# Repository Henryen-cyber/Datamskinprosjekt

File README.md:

# Datamaskinprosjekt

Bitstreams for FPGA are located [here](./FPGA/bitstreams/).

Hex for MCU are packaged in the Github releases.

## [The Report](./Rapport_Gruppe2_TDT4295_Datamaskinprosjekt.pdf)

## PCB KiCAD Checkout

When working on a KiCAD File ALWAYS update this table to state that you are working on it

| KiCAD File | Checkout Status          | Checkout/-in Date | Checked out by |
| ---------- | ------------------------ | ----------------- | -------------- |
| Example1   | :red_circle: Checked Out | 12.11.2023        | John Doe       |
| Example2   | :green_circle: Available | 01.09.2023        | Jane Doe       |

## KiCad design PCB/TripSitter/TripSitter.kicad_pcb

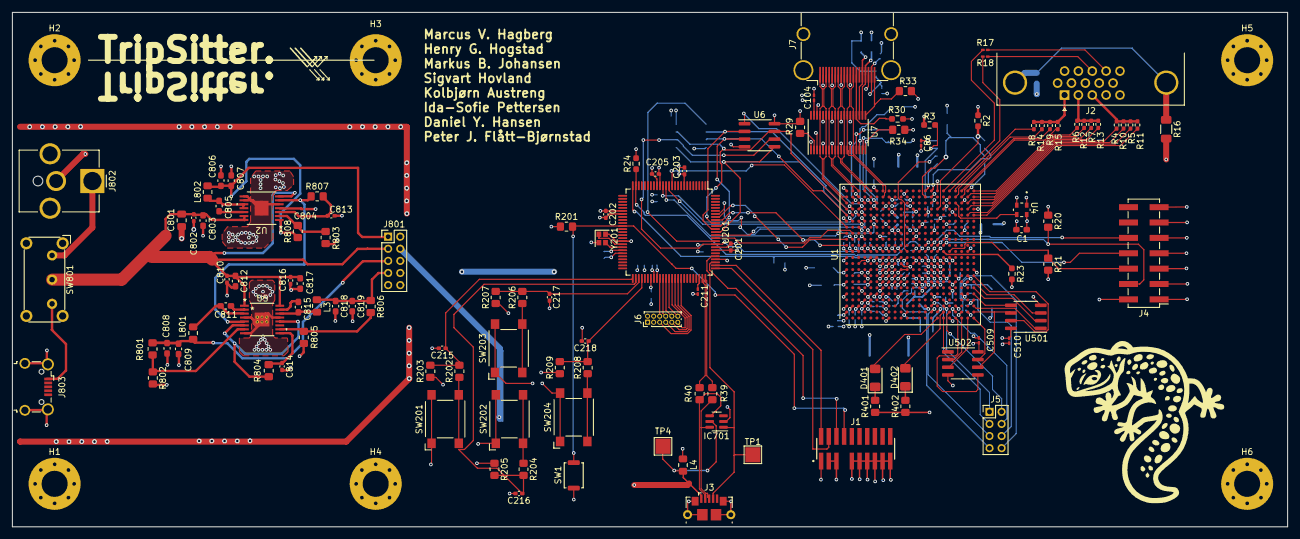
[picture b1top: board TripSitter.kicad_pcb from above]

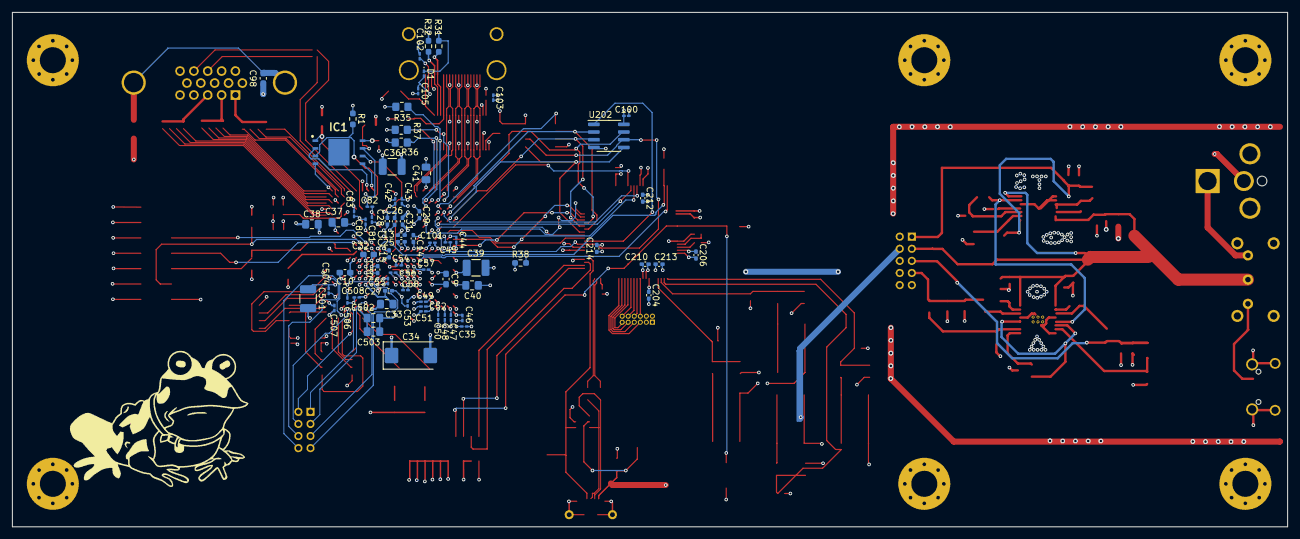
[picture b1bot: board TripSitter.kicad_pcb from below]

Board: 4 copper layers, 210.7 x 85.0 mm, 192 parts (72 on the bottom side), 147 nets.

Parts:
C1, C803, C805, C811, C812, C815, C817: 0.1uF; C_0603_1608Metric_Pad1.08x0.95mm_HandSolder
C9, C10, C32: 47uF; C_0603_1608Metric_Pad1.08x0.95mm_HandSolder
C13, C14, C15, C25, C26, C27, C30: 470nF; C_0402_1005Metric_Pad0.74x0.62mm_HandSolder
C28, C29, C31: 4.7uF; C_0402_1005Metric_Pad0.74x0.62mm_HandSolder
C33, C801: 100uF; C_0805_2012Metric_Pad1.18x1.45mm_HandSolder
C34: 330uF; CP_EIA-7343-43_Kemet-X_Pad2.25x2.55mm_HandSolder
C35, C46, C47, C48, C49, C50: 4.7uF; C_0201_0603Metric_Pad0.64x0.40mm_HandSolder
C36, C39, C501: 47uF; C_1210_3225Metric_Pad1.33x2.70mm_HandSolder
C37, C38, C40, C41, C502, C503: 4.7uF; C_0805_2012Metric_Pad1.18x1.45mm_HandSolder
C42, C43, C44, C45, C51, C52, C53, C54, C55, C56, C57, C58, C80, C81, C82, C83, C504, C506, C507, C508: 470nF; C_0201_0603Metric_Pad0.64x0.40mm_HandSolder
C86: 100nF; C_0201_0603Metric_Pad0.64x0.40mm_HandSolder
C98: 1nF; C_0603_1608Metric_Pad1.08x0.95mm_HandSolder
C100, C101, C102, C103, C104, C105, C509, C510: 0.1uF; C_0201_0603Metric_Pad0.64x0.40mm_HandSolder
C201, C214, C802, C810, C816: 10uF; C_0402_1005Metric_Pad0.74x0.62mm_HandSolder
C202, C203, C204, C205, C206, C212, C213, C215, C216, C217, C218: 0.1uF; C_0402_1005Metric_Pad0.74x0.62mm_HandSolder
C210, C813, C814: 1uF; C_0402_1005Metric_Pad0.74x0.62mm_HandSolder
C211: 1uF; C_0201_0603Metric_Pad0.64x0.40mm_HandSolder
C804: 3.3nF; C_0201_0603Metric_Pad0.64x0.40mm_HandSolder
C806, C807, C808, C809, C818, C819: 22uF; C_0603_1608Metric_Pad1.08x0.95mm_HandSolder
D1: D; D_0201_0603Metric_Pad0.64x0.40mm_HandSolder
D401, D402: LED; LED_1206_3216Metric_Pad1.42x1.75mm_HandSolder
H1, H2, H3, H4, H5, H6: MountingHole_Pad; MountingHole_4.3mm_M4_Pad_Via
IC1: MT25QL256ABA1EW9-0SIT; SON127P800X600X80-9N-D
IC701: IP4220CZ6; SC-74-6_1.5x2.9mm_P0.95mm
J1: FTSH-110-01-L-DV-007; SAMTEC_FTSH-110-01-L-DV-007
J2: DE15_Plug_HighDensity_MountingHoles; DSUB-15-HD_Female_Horizontal_P2.29x1.98mm_EdgePinOffset3.03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
J3: USB_B_Micro; USB_Micro-B_GCT_USB3076-30-A
J4: Conn_02x07_Odd_Even; PinHeader_2x07_P2.54mm_Vertical_SMD
J5: Conn_02x04_Counter_Clockwise; PinHeader_2x04_P2.00mm_Vertical
J6: EFM32_PinHeader_PortE; PinHeader_2x06_P1.00mm_Vertical
J7: HDMI_A_1.4; HDMI_A_Molex_208658-1001_Horizontal
J801: Conn_02x05_Odd_Even; PinHeader_2x05_P2.00mm_Vertical
J802: Jack-DC; BarrelJack_CUI_PJ-063AH_Horizontal_CircularHoles
J803: USB_B_Micro; USB_Micro-B_Wuerth_629105150521_CircularHoles
L3: 2.2uH; L_0805_2012Metric_Pad1.15x1.40mm_HandSolder
L4: CBF221HC; L_0805_2012Metric_Pad1.15x1.40mm_HandSolder
L801, L802: 1.5uH; L_0805_2012Metric_Pad1.15x1.40mm_HandSolder
R1, R3, R23, R24, R31, R32: 4.7k; R_0603_1608Metric_Pad0.98x0.95mm_HandSolder
R2: 2.4k; R_0603_1608Metric_Pad0.98x0.95mm_HandSolder
R4, R6, R8: 4k; R_0402_1005Metric_Pad0.72x0.64mm_HandSolder
R5, R7, R9: 1K; R_0402_1005Metric_Pad0.72x0.64mm_HandSolder
R10, R12, R14: 2k; R_0402_1005Metric_Pad0.72x0.64mm_HandSolder
R11, R13, R15: 510; R_0402_1005Metric_Pad0.72x0.64mm_HandSolder
R16: 1M; R_1206_3216Metric_Pad1.30x1.75mm_HandSolder
R17, R18: 100; R_0201_0603Metric_Pad0.64x0.40mm_HandSolder
R20, R21, R29, R33, R203, R205, R207, R209: 10k; R_0805_2012Metric_Pad1.20x1.40mm_HandSolder
R30: 27k; R_0603_1608Metric_Pad0.98x0.95mm_HandSolder
R34, R35, R36, R37: 47k; R_0805_2012Metric_Pad1.20x1.40mm_HandSolder
R38: 330k; R_0603_1608Metric_Pad0.98x0.95mm_HandSolder
R39, R40: 15R; R_0805_2012Metric_Pad1.20x1.40mm_HandSolder
R201, R804: 100K; R_0805_2012Metric_Pad1.20x1.40mm_HandSolder
R202, R204, R206, R208: 1k; R_0805_2012Metric_Pad1.20x1.40mm_HandSolder
R401, R402: 220; R_0805_2012Metric_Pad1.20x1.40mm_HandSolder
R801: 30.1K; R_0805_2012Metric_Pad1.20x1.40mm_HandSolder
R802, R803, R805: 22.1K; R_0805_2012Metric_Pad1.20x1.40mm_HandSolder
R806: 73.2K; R_0805_2012Metric_Pad1.20x1.40mm_HandSolder
R807: 100k; R_0805_2012Metric_Pad1.20x1.40mm_HandSolder
R808: 6.81k; R_0805_2012Metric_Pad1.20x1.40mm_HandSolder
SW1: SW_Push_Open; SW_Push_SPST_NO_Alps_SKRK
SW201, SW202, SW203, SW204: SW_Push; SW_SPST_Omron_B3FS-100xP
SW801: SW_DPDT_x2; SW_E-Switch_EG1224_SPDT_Angled
TP1: ID_Probe; TestPoint_Pad_2.5x2.5mm
TP4: VBUS_Probe; TestPoint_Pad_2.5x2.5mm
U1: XC7A100T-FGG484; Xilinx_FGG484
U2: TPS54325_PWP_14; PWP14_2P31X2P46
U4: DSC1001DL5-100.0000T; CDFN4_2P5X2_MCH-L
U5: TPS54294PWP; PWP16_2P31X2P46
U6, U202, U501, U502: IS62WVS2568FBLL-20NLI; SOIC-8_3.9x4.9mm_P1.27mm
U7: TPD12S520DBT; TSSOP-38_4.4x9.7mm_P0.5mm
U201: EFM32GG11B420F2048GQ100; TQFP-100_14x14mm_P0.5mm
Y201: 48MHz; Crystal_SMD_2016-4Pin_2.0x1.6mm

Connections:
+1V0: C27.1, C30.1, C33.1, C34.2, C35.1, C46.1, C47.1, C48.1, C49.1, C50.1, C51.1, C52.1, C53.1, C54.1, C55.1, C56.1, C57.1, C58.1, J801.2, U1.H8 (VCCINT), U1.H10 (VCCINT), U1.J7 (VCCINT), U1.J9 (VCCINT), U1.J11 (VCCBRAM), U1.K8 (VCCINT), U1.L7 (VCCINT), U1.L11 (VCCBRAM), U1.M8 (VCCINT), U1.N7 (VCCINT), U1.N11 (VCCBRAM), U1.P8 (VCCINT), U1.P10 (VCCINT), U1.R7 (VCCINT), U1.R9 (VCCINT), U1.T8 (VCCINT), U1.T10 (VCCINT)
+1V8: C13.1, C14.1, C15.1, C25.1, C26.1, C28.1, C29.1, C31.1, C32.1, J801.6, U1.H12 (VCCAUX), U1.K10 (VCCADC_0), U1.K12 (VCCAUX), U1.M12 (VCCAUX), U1.P12 (VCCAUX), U1.R11 (VCCAUX)
+3.3V: C1.2, C9.1, C10.1, C36.1, C37.1, C38.1, C39.1, C40.1, C41.1, C42.1, C43.1, C44.1, C45.1, C80.1, C81.1, C82.1, C83.1, C86.1, C100.1, C101.1, C103.2, C201.1, C202.1, C203.1, C204.1, C205.1, C206.1, C212.1, C213.1, C214.1, C501.1, C502.1, C503.1, C504.1, C506.1, C507.1, C508.1, C509.1, C510.1, IC1.8 (VCC), J1.01, J4.2, J801.8, R1.1, R2.1, R3.1, R20.1, R21.2, R23.2, R24.2, R29.1, R30.1, R34.2, R35.2, R36.2, R37.2, R38.1, R201.1, R203.1, R205.1, R207.1, R209.1, U1.A17 (VCCO_16), U1.AA7 (VCCO_34), U1.AB4 (VCCO_34), U1.B14 (VCCO_16), U1.C21 (VCCO_16), U1.D18 (VCCO_16), U1.E15 (VCCO_16), U1.F12 (VCCO_0), U1.F22 (VCCO_16), U1.M14 (VCCO_14), U1.P18 (VCCO_14), U1.R5 (VCCO_34), U1.R15 (VCCO_14), U1.T2 (VCCO_34), U1.T12 (VCCO_0), U1.T22 (VCCO_14), U1.U8 (CFGBVS_0), U1.U11 (M0_0), U1.U19 (VCCO_14), U1.V6 (VCCO_34), U1.W3 (VCCO_34), U1.Y20 (VCCO_14), U4.1 (*STANDBY), U4.4 (VDD), U6.8 (VCC), U201.8 (IOVDD0), U201.17 (IOVDD0), U201.31 (IOVDD0), U201.44 (IOVDD0), U201.57 (DVDD), U201.82 (IOVDD0), U202.8 (VCC), U501.8 (VCC), U502.8 (VCC)
+5V: C102.2, C105.1, D1.2 (A), IC701.5 (VP), J3.1 (VBUS), J7.18 (+5V), J801.4, L4.2, TP4.1, U7.1 (5V_SUPPLY)
/FPGA Artix-7 100T 1FGG484C/DDR3/FPGA_LED_INDICATOR_1: D401.2 (A), U1.T1 (IO_L1P_T0_34)
/FPGA Artix-7 100T 1FGG484C/DDR3/FPGA_LED_INDICATOR_2: D402.2 (A), U1.U2 (IO_L2P_T0_34)
/FPGA Artix-7 100T 1FGG484C/DDR3/FPGA_PINOUT_1: J5.1, U1.U3 (IO_L6P_T0_34)
/FPGA Artix-7 100T 1FGG484C/DDR3/FPGA_PINOUT_2: J5.2, U1.V2 (IO_L2N_T0_34)
/FPGA Artix-7 100T 1FGG484C/DDR3/FPGA_PINOUT_3: J5.3, U1.R3 (IO_L3P_T0_DQS_34)
/FPGA Artix-7 100T 1FGG484C/DDR3/FPGA_PINOUT_4: J5.4, U1.W2 (IO_L4P_T0_34)
/FPGA Artix-7 100T 1FGG484C/DDR3/FPGA_PINOUT_5: J5.5, U1.R2 (IO_L3N_T0_DQS_34)
/FPGA Artix-7 100T 1FGG484C/DDR3/FPGA_PINOUT_6: J5.6, U1.AA8 (IO_L22P_T3_34)
/FPGA Artix-7 100T 1FGG484C/DDR3/FPGA_PINOUT_7: J5.7, U1.W7 (IO_L19N_T3_VREF_34)
/FPGA Artix-7 100T 1FGG484C/DDR3/FPGA_PINOUT_8: J5.8, U1.Y2 (IO_L4N_T0_34)
/FPGA Artix-7 100T 1FGG484C/DDR3/SRAM_QSPI1_CS0: U1.AB3 (IO_L8P_T1_34), U501.1 (CS#)
/FPGA Artix-7 100T 1FGG484C/DDR3/SRAM_QSPI1_DQ0: U1.AB5 (IO_L10N_T1_34), U501.5 (SIO0)
/FPGA Artix-7 100T 1FGG484C/DDR3/SRAM_QSPI1_DQ1: U1.AB6 (IO_L20N_T3_34), U501.2 (SIO1)
/FPGA Artix-7 100T 1FGG484C/DDR3/SRAM_QSPI1_DQ2: U1.AB7 (IO_L20P_T3_34), U501.3 (SIO2)
/FPGA Artix-7 100T 1FGG484C/DDR3/SRAM_QSPI1_DQ3: U1.AB8 (IO_L22N_T3_34), U501.7 (SIO3)
/FPGA Artix-7 100T 1FGG484C/DDR3/SRAM_QSPI2_CS0: U1.U1 (IO_L1N_T0_34), U502.1 (CS#)
/FPGA Artix-7 100T 1FGG484C/DDR3/SRAM_QSPI2_DQ0: U1.W1 (IO_L5P_T0_34), U502.5 (SIO0)
/FPGA Artix-7 100T 1FGG484C/DDR3/SRAM_QSPI2_DQ1: U1.Y1 (IO_L5N_T0_34), U502.2 (SIO1)
/FPGA Artix-7 100T 1FGG484C/DDR3/SRAM_QSPI2_DQ2: U1.AA1 (IO_L7P_T1_34), U502.3 (SIO2)
/FPGA Artix-7 100T 1FGG484C/DDR3/SRAM_QSPI2_DQ3: U1.AB1 (IO_L7N_T1_34), U502.7 (SIO3)
/FPGA Artix-7 100T 1FGG484C/DDR3/SRAM_QSPIX_SCLK: U1.AB2 (IO_L8N_T1_34), U501.6 (SCK), U502.6 (SCK)
/FPGA Artix-7 100T 1FGG484C/GCLK100: U1.W20 (IO_L12N_T1_MRCC_14), U4.3 (OUT)
/FPGA Artix-7 100T 1FGG484C/HDMI Connector/CEC: J7.13 (CEC), R30.2, U7.23 (CE_REMOTE_OUT)
/FPGA Artix-7 100T 1FGG484C/Programmer interface/QSPI_CS: IC1.1 (S#), R2.2, U1.T19 (IO_L6P_T0_FCS_B_14)
/FPGA Artix-7 100T 1FGG484C/Programmer interface/QSPI_DQ0: IC1.5 (DQ0), U1.P22 (IO_L1P_T0_D00_MOSI_14)
/FPGA Artix-7 100T 1FGG484C/Programmer interface/QSPI_DQ1: IC1.2 (DQ1), U1.R22 (IO_L1N_T0_D01_DIN_14)
/FPGA Artix-7 100T 1FGG484C/Programmer interface/QSPI_DQ2: IC1.3 (W#/DQ2), R1.2, U1.P21 (IO_L2P_T0_D02_14)
/FPGA Artix-7 100T 1FGG484C/Programmer interface/QSPI_DQ3: IC1.7 (DQ3/HOLD#), R3.2, U1.R21 (IO_L2N_T0_D03_14)
/FPGA Artix-7 100T 1FGG484C/QSPI0_DQ0: U1.B17 (IO_L11P_T1_SRCC_16), U6.5 (SIO0), U201.88 (PD9), U202.5 (SIO0)
/FPGA Artix-7 100T 1FGG484C/QSPI0_DQ1: U1.B18 (IO_L11N_T1_SRCC_16), U6.2 (SIO1), U201.89 (PD10), U202.2 (SIO1)
/FPGA Artix-7 100T 1FGG484C/QSPI0_DQ2: U1.A18 (IO_L17P_T2_16), U6.3 (SIO2), U201.90 (PD11), U202.3 (SIO2)
/FPGA Artix-7 100T 1FGG484C/QSPI0_DQ3: U1.A19 (IO_L17N_T2_16), U6.7 (SIO3), U201.91 (PD12), U202.7 (SIO3)
/FPGA Artix-7 100T 1FGG484C/QSPI0_DQ4: U1.A16 (IO_L9N_T1_DQS_16), U201.12 (PB3)
/FPGA Artix-7 100T 1FGG484C/QSPI0_DQ5: U1.C17 (IO_L12N_T1_MRCC_16), U201.13 (PB4)
/FPGA Artix-7 100T 1FGG484C/QSPI0_DQ6: U1.A15 (IO_L9P_T1_DQS_16), U201.14 (PB5)
/FPGA Artix-7 100T 1FGG484C/QSPI0_DQ7: U1.C18 (IO_L13P_T2_MRCC_16), U201.15 (PB6)
/FPGA Artix-7 100T 1FGG484C/SRAM_QSPI0_CS0: U1.C19 (IO_L13N_T2_MRCC_16), U6.1 (CS#)
/FPGA Artix-7 100T 1FGG484C/SRAM_QSPI0_SCLK: U1.D14 (IO_L6P_T0_16), U6.6 (SCK), U201.84 (PF6), U202.6 (SCK)
/FPGA Artix-7 100T 1FGG484C/VGA_B0: R4.1, U1.AB20 (IO_L15N_T2_DQS_DOUT_CSO_B_14)
/FPGA Artix-7 100T 1FGG484C/VGA_B1: R10.1, U1.AA19 (IO_L15P_T2_DQS_RDWR_B_14)
/FPGA Artix-7 100T 1FGG484C/VGA_B2: R5.1, U1.AA18 (IO_L17P_T2_A14_D30_14)
/FPGA Artix-7 100T 1FGG484C/VGA_B3: R11.1, U1.AB18 (IO_L17N_T2_A13_D29_14)
/FPGA Artix-7 100T 1FGG484C/VGA_G0: R6.1, U1.AB22 (IO_L10N_T1_D15_14)
/FPGA Artix-7 100T 1FGG484C/VGA_G1: R12.1, U1.AA21 (IO_L8N_T1_D12_14)
/FPGA Artix-7 100T 1FGG484C/VGA_G2: R7.1, U1.AB21 (IO_L10P_T1_D14_14)
/FPGA Artix-7 100T 1FGG484C/VGA_G3: R13.1, U1.AA20 (IO_L8P_T1_D11_14)
/FPGA Artix-7 100T 1FGG484C/VGA_HSync: R17.2, U1.U22 (IO_L3P_T0_DQS_PUDC_B_14)
/FPGA Artix-7 100T 1FGG484C/VGA_R0: R8.1, U1.W22 (IO_L7N_T1_D10_14)
/FPGA Artix-7 100T 1FGG484C/VGA_R1: R14.1, U1.W21 (IO_L7P_T1_D09_14)
/FPGA Artix-7 100T 1FGG484C/VGA_R2: R9.1, U1.Y22 (IO_L9N_T1_DQS_D13_14)
/FPGA Artix-7 100T 1FGG484C/VGA_R3: R15.1, U1.Y21 (IO_L9P_T1_DQS_14)
/FPGA Artix-7 100T 1FGG484C/VGA_VSync: R18.2, U1.V22 (IO_L3N_T0_DQS_EMCCLK_14)
/MCU EFM32GG11B420/PD5_BUTTON: C215.1, R202.2, R203.2, U201.51 (PD5)
/MCU EFM32GG11B420/PD6_BUTTON: C216.1, R204.2, R205.2, U201.52 (PD6)
/MCU EFM32GG11B420/PD7_BUTTON: C217.1, R206.2, R207.2, U201.53 (PD7)
/MCU EFM32GG11B420/PD8_BUTTON: C218.1, R208.2, R209.2, U201.54 (PD8)
/MCU EFM32GG11B420/PE0_UART0_TX: J6.6, U201.60 (PE0)
/MCU EFM32GG11B420/PE1_UART0_RX: J6.8, U201.61 (PE1)
/MCU EFM32GG11B420/PE2_UART0_CTS: J6.10, U201.62 (PE2)
/MCU EFM32GG11B420/PE3_UART0_RTS: J6.12, U201.63 (PE3)
/MCU EFM32GG11B420/PE_4: J6.11, U201.64 (PE4)
/MCU EFM32GG11B420/PE_5: J6.9, U201.65 (PE5)
/MCU EFM32GG11B420/PE_6: J6.7, U201.66 (PE6)
/MCU EFM32GG11B420/PE_7: J6.5, U201.67 (PE7)
/MCU EFM32GG11B420/PF12: IC701.1 (I/O_1), J3.4 (ID), TP1.1, U201.80 (PF12)
/MCU EFM32GG11B420/QSPI0_CS0: U201.85 (PF7), U202.1 (CS#)
/MCU EFM32GG11B420/QSPI0_CS1: U1.B15 (IO_L7P_T1_16), U201.86 (PF8)
/MCU EFM32GG11B420/QSPI0_DQS: U1.D17 (IO_L12P_T1_MRCC_16), U201.87 (PF9)
/MCU EFM32GG11B420/USB3_micro_ab/D+: IC701.4 (I/O_3), J3.2 (D-), R40.2
/MCU EFM32GG11B420/USB3_micro_ab/D-: IC701.6 (I/O_4), J3.3 (D+), R39.1
/MCU EFM32GG11B420/USB_D+: R40.1, U201.74 (PF10)
/MCU EFM32GG11B420/USB_D-: R39.2, U201.75 (PF11)
/MCU EFM32GG11B420/VBUS: L4.1, U201.79 (VBUS)
/PCB Power System/1V0: C806.2, C807.2, J801.1, L802.2, R808.1, U2.1 (VO)
/PCB Power System/1V8: C808.2, C809.2, J801.5, L801.1, R801.1
/PCB Power System/3V3: C818.2, C819.2, J801.7, L3.2, R806.1
/PCB Power System/5V0: C801.1, C802.1, C803.1, C810.1, C812.1, C816.1, C817.1, J801.3, SW801.2 (B), U2.7 (EN), U2.13 (VIN), U2.14 (VCC), U5.1 (VIN1), U5.16 (VIN2)
EFM32_RESETN: J1.08, R201.2, SW1.2 (B), U201.36 (RESETN)
FPGA_DONE: R38.2, U1.G11 (DONE_0), U201.25 (PB8)
FPGA_PROGRAM_B: R24.1, U1.N12 (PROGRAM_B_0), U201.24 (PB7)
GND: C1.1, C9.2, C10.2, C13.2, C14.2, C15.2, C25.2, C26.2, C27.2, C28.2, C29.2, C30.2, C31.2, C32.2, C33.2, C34.1, C35.2, C36.2, C37.2, C38.2, C39.2, C40.2, C41.2, C42.2, C43.2, C44.2, C45.2, C46.2, C47.2, C48.2, C49.2, C50.2, C51.2, C52.2, C53.2, C54.2, C55.2, C56.2, C57.2, C58.2, C80.2, C81.2, C82.2, C83.2, C86.2, C98.2, C100.2, C101.2, C102.1, C103.1, C104.2, C105.2, C201.2, C202.2, C203.2, C204.2, C205.2, C206.2, C210.2, C211.2, C212.2, C213.2, C214.2, C215.2, C216.2, C217.2, C218.2, C501.2, C502.2, C503.2, C504.2, C506.2, C507.2, C508.2, C509.2, C510.2, C801.2, C802.2, C803.2, C804.2, C806.1, C807.1, C808.1, C809.1, C810.2, C812.2, C813.2, C814.2, C816.2, C817.2, C818.1, C819.1, H1.1, H2.1, H3.1, H4.1, H5.1, H6.1, IC1.4 (VSS), IC701.2 (GND), J1.03, J1.05, J1.09, J1.11, J1.13, J1.15, J1.17, J1.19, J2.5, J2.6, J2.7, J2.8, J2.10, J3.6 (Shield), J4.1, J4.3, J4.5, J4.7, J4.9, J4.11, J4.13, J7.2 (D2S), J7.5 (D1S), J7.8 (D0S), J7.11 (CKS), J7.17 (GND), J7.SH, J802.2, J803.6 (Shield), R16.2, R33.2, R401.1, R402.1, R802.2, R803.2, R805.2, SW1.1 (A), SW201.1, SW202.1, SW203.1, SW204.1, U1.A2 (GND), U1.A3 (GND), U1.A5 (GND), U1.A7 (GND), U1.A9 (GND), U1.A11 (GND), U1.A12 (GND), U1.A22 (GND), U1.AA2 (GND), U1.AA12 (GND), U1.AA22 (GND), U1.AB9 (GND), U1.AB19 (GND), U1.B3 (GND), U1.B12 (GND), U1.B19 (GND), U1.C3 (GND), U1.C6 (GND), U1.C10 (GND), U1.C12 (GND), U1.C16 (GND), U1.D3 (GND), U1.D4 (GND), U1.D8 (GND), U1.D12 (GND), U1.D13 (GND), U1.E4 (GND), U1.E5 (GND), U1.E7 (GND), U1.E9 (GND), U1.E11 (GND), U1.E12 (VCCBATT_0), U1.E20 (GND), U1.F5 (GND), U1.F11 (GND), U1.F17 (GND), U1.G5 (GND), U1.G6 (GND), U1.G7 (GND), U1.G8 (GND), U1.G9 (GND), U1.G10 (GND), U1.G12 (GND), U1.G14 (GND), U1.H1 (GND), U1.H7 (GND), U1.H9 (GND), U1.H11 (GND), U1.H21 (GND), U1.J8 (GND), U1.J10 (GND), U1.J12 (GND), U1.J18 (GND), U1.K5 (GND), U1.K7 (GND), U1.K9 (GNDADC_0), U1.K11 (GND), U1.K15 (GND), U1.L2 (GND), U1.L8 (GND), U1.L9 (VREFN_0), U1.L22 (GND), U1.M7 (GND), U1.M10 (VREFP_0), U1.M11 (GND), U1.M19 (GND), U1.N6 (GND), U1.N8 (GND), U1.N16 (GND), U1.P3 (GND), U1.P7 (GND), U1.P9 (GND), U1.P11 (GND), U1.P13 (GND), U1.R8 (GND), U1.R10 (GND), U1.R12 (GND), U1.R20 (GND), U1.T7 (GND), U1.T9 (GND), U1.T11 (GND), U1.T17 (GND), U1.U4 (GND), U1.U9 (M2_0), U1.U10 (M1_0), U1.U14 (GND), U1.V1 (GND), U1.V11 (GND), U1.V21 (GND), U1.W8 (GND), U1.W18 (GND), U1.Y5 (GND), U1.Y15 (GND), U2.5 (GND), U2.8 (PGND1), U2.9 (PGND2), U2.15 (EPAD), U4.2 (GND), U5.4 (PGND1), U5.8 (GND), U5.13 (PGND2), U5.EPAD, U6.4 (VSS), U7.3 (GND), U7.5 (TMDS_GND), U7.8 (TMDS_GND), U7.11 (TMDS_GND), U7.14 (TMDS_GND), U7.25 (TMDS_GND), U7.28 (TMDS_GND), U7.31 (TMDS_GND), U7.34 (TMDS_GND), U7.36 (GND), U201.16 (VSS), U201.32 (VSS), U201.41 (AVDD), U201.45 (AVDD), U201.58 (VSS), U201.83 (VSS), U202.4 (VSS), U501.4 (VSS), U502.4 (VSS), Y201.2, Y201.4
HDMI_CEC: R37.1, U1.B21 (IO_L21P_T3_DQS_16), U7.16 (CE_REMOTE_IN)
HDMI_CLK_N: J7.12 (CK-), U1.G21 (IO_L24P_T3_16), U7.15 (TMDS_CK-), U7.24 (TMDS_CK-)
HDMI_CLK_P: J7.10 (CK+), U1.G22 (IO_L24N_T3_16), U7.13 (TMDS_CK+), U7.26 (TMDS_CK+)
HDMI_HPD: R34.1, U1.F19 (IO_L18P_T2_16), U7.19 (HOTPLUG_DET_IN)
HDMI_SCL: R35.1, U1.D20 (IO_L19P_T3_16), U7.17 (DDC_CLK_IN)
HDMI_SDA: R36.1, U1.F20 (IO_L18N_T2_16), U7.18 (DDC_DAT_IN)
HDMI_TX0_N: J7.9 (D0-), U1.E22 (IO_L22P_T3_16), U7.12 (TMDS_D0-), U7.27 (TMDS_D0-)
HDMI_TX0_P: J7.7 (D0+), U1.D22 (IO_L22N_T3_16), U7.10 (TMDS_D0+), U7.29 (TMDS_D0+)
HDMI_TX1_N: J7.6 (D1-), U1.C22 (IO_L20P_T3_16), U7.9 (TMDS_D1-), U7.30 (TMDS_D1-)
HDMI_TX1_P: J7.4 (D1+), U1.B22 (IO_L20N_T3_16), U7.7 (TMDS_D1+), U7.32 (TMDS_D1+)
HDMI_TX2_N: J7.3 (D2-), U1.A21 (IO_L21N_T3_DQS_16), U7.6 (TMDS_D2-), U7.33 (TMDS_D2-)
HDMI_TX2_P: J7.1 (D2+), U1.A20 (IO_L16N_T2_16), U7.4 (TMDS_D2+), U7.35 (TMDS_D2+)
MCU_PE7: U1.A13 (IO_L10P_T1_16), U201.92 (PE8)
MCU_PE8: U1.A14 (IO_L10N_T1_16), U201.93 (PE9)
MCU_PE9: U1.F16 (IO_L2P_T0_16), U201.94 (PE10)
unnamed: C98.1, J2.0, R16.1
unnamed: D1.1 (K), R31.1, R32.1
unnamed: D401.1 (K), R401.2
unnamed: D402.1 (K), R402.2
unnamed: IC1.6 (C), U1.L12 (CCLK_0)
unnamed: J2.1, R8.2, R9.2, R14.2, R15.2
unnamed: J2.2, R6.2, R7.2, R12.2, R13.2
unnamed: J2.3, R4.2, R5.2, R10.2, R11.2
unnamed: J2.13, R18.1
unnamed: J2.14, R17.1
unnamed: J4.4, R20.2, U1.T13 (TMS_0)
unnamed: J4.6, R21.1, U1.V12 (TCK_0)
unnamed: J4.8, U1.U13 (TDO_0)
unnamed: J4.10, U1.R13 (TDI_0)
unnamed: J7.19 (HPD/HEAC-), R33.1, U7.20 (HOTPLUG_DET_OUT)
unnamed: J7.15 (SCL), R31.2, U7.22 (DDC_CLK_OUT)
unnamed: J7.16 (SDA), R32.2, U7.21 (DDC_DAT_OUT)
unnamed: J803.1 (VBUS), SW801.3 (C)
unnamed: R202.1, SW201.2
unnamed: R204.1, SW202.2
unnamed: R206.1, SW203.2
unnamed: R208.1, SW204.2
unnamed: J802.1, SW801.1 (A)
unnamed: R23.1, U1.U12 (INIT_B_0)
unnamed: R807.1, U2.6 (PG), U5.5 (EN1)
unnamed: C804.1, U2.4 (SS)
unnamed: C805.1, L802.1, U2.10 (SW1), U2.11 (SW2)
unnamed: C805.2, U2.12 (VBST)
unnamed: R803.1, R808.2, U2.2 (VFB)
unnamed: C813.1, R807.2, U2.3 (VREG5)
unnamed: R804.2, U5.6 (PG1), U5.12 (EN2)
unnamed: C811.2, L801.2, U5.3 (SW1)
unnamed: C815.2, L3.1, U5.14 (SW2)
unnamed: C811.1, U5.2 (VBST1)
unnamed: C815.1, U5.15 (VBST2)
unnamed: R801.2, R802.1, U5.7 (VFB1)
unnamed: R805.1, R806.2, U5.10 (VFB2)
unnamed: C814.1, R804.1, U5.9 (VREG5)
unnamed: C104.1, U7.37 (ESD_BYP)
unnamed: R29.2, U7.2 (LV_SUPPLY)
unnamed: U201.42 (PB13), Y201.1
unnamed: U201.43 (PB14), Y201.3
unnamed: J1.04, U201.76 (PF0)
unnamed: J1.02, U201.77 (PF1)
unnamed: J1.06, U201.78 (PF2)
unnamed: C210.1, U201.59 (DECOUPLE)
unnamed: C211.1, U201.73 (VREGO)

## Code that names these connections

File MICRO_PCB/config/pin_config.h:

#ifndef PIN_CONFIG_H
#define PIN_CONFIG_H

// $[ACMP0]
// [ACMP0]$

// $[ACMP1]
// [ACMP1]$

// $[ACMP2]
// [ACMP2]$

// $[ACMP3]
// [ACMP3]$

// $[ADC0]
// [ADC0]$

// $[ADC1]
// [ADC1]$

// $[BU]
// [BU]$

// $[CAN0]
// [CAN0]$

// $[CAN1]
// [CAN1]$

// $[CMU]
// [CMU]$

// $[CSEN]
// [CSEN]$

// $[DBG]
// [DBG]$

// $[EBI]
// [EBI]$

// $[ETH]
// [ETH]$

// $[ETM]
// [ETM]$

// $[GPIO]
// [GPIO]$

// $[I2C0]
// [I2C0]$

// $[I2C1]
// [I2C1]$

// $[I2C2]
// [I2C2]$

// $[IDAC0]
// [IDAC0]$

// $[LCD]
// [LCD]$

// $[LESENSE]
// [LESENSE]$

// $[LETIMER0]
// [LETIMER0]$

// $[LETIMER1]
// [LETIMER1]$

// $[LEUART0]
// [LEUART0]$

// $[LEUART1]
// [LEUART1]$

// $[LFXO]
// [LFXO]$

// $[PCNT0]
// [PCNT0]$

// $[PCNT1]
// [PCNT1]$

// $[PCNT2]
// [PCNT2]$

// $[PRS.CH0]
// [PRS.CH0]$

// $[PRS.CH1]
// [PRS.CH1]$

// $[PRS.CH2]
// [PRS.CH2]$

// $[PRS.CH3]
// [PRS.CH3]$

// $[PRS.CH4]
// [PRS.CH4]$

// $[PRS.CH5]
// [PRS.CH5]$

// $[PRS.CH6]
// [PRS.CH6]$

// $[PRS.CH7]
// [PRS.CH7]$

// $[PRS.CH8]
// [PRS.CH8]$

// $[PRS.CH9]
// [PRS.CH9]$

// $[PRS.CH10]
// [PRS.CH10]$

// $[PRS.CH11]
// [PRS.CH11]$

// $[PRS.CH12]
// [PRS.CH12]$

// $[PRS.CH13]
// [PRS.CH13]$

// $[PRS.CH14]
// [PRS.CH14]$

// $[PRS.CH15]
// [PRS.CH15]$

// $[PRS.CH16]
// [PRS.CH16]$

// $[PRS.CH17]
// [PRS.CH17]$

// $[PRS.CH18]
// [PRS.CH18]$

// $[PRS.CH19]
// [PRS.CH19]$

// $[PRS.CH20]
// [PRS.CH20]$

// $[PRS.CH21]
// [PRS.CH21]$

// $[PRS.CH22]
// [PRS.CH22]$

// $[PRS.CH23]
// [PRS.CH23]$

// $[QSPI0]
// [QSPI0]$

// $[SDIO]
// [SDIO]$

// $[TIMER0]
// [TIMER0]$

// $[TIMER1]
// [TIMER1]$

// $[TIMER2]
// [TIMER2]$

// $[TIMER3]
// [TIMER3]$

// $[TIMER4]
// [TIMER4]$

// $[TIMER5]
// [TIMER5]$

// $[TIMER6]
// [TIMER6]$

// $[UART0]
// [UART0]$

// $[UART1]
// [UART1]$

// $[USART0]
// [USART0]$

// $[USART1]
// [USART1]$

// $[USART2]
// USART2 CLK on PB5
#ifndef USART2_CLK_PORT                         
#define USART2_CLK_PORT                          gpioPortB
#endif
#ifndef USART2_CLK_PIN                          
#define USART2_CLK_PIN                           5
#endif
#ifndef USART2_CLK_LOC                          
#define USART2_CLK_LOC                           1
#endif

// USART2 CS on PB6
#ifndef USART2_CS_PORT                          
#define USART2_CS_PORT                           gpioPortB
#endif
#ifndef USART2_CS_PIN                           
#define USART2_CS_PIN                            6
#endif
#ifndef USART2_CS_LOC                           
#define USART2_CS_LOC                            1
#endif

// USART2 RX on PB4
#ifndef USART2_RX_PORT                          
#define USART2_RX_PORT                           gpioPortB
#endif
#ifndef USART2_RX_PIN                           
#define USART2_RX_PIN                            4
#endif
#ifndef USART2_RX_LOC                           
#define USART2_RX_LOC                            1
#endif

// USART2 TX on PB3
#ifndef USART2_TX_PORT                          
#define USART2_TX_PORT                           gpioPortB
#endif
#ifndef USART2_TX_PIN                           
#define USART2_TX_PIN                            3
#endif
#ifndef USART2_TX_LOC                           
#define USART2_TX_LOC                            1
#endif

// [USART2]$

// $[USART3]
// [USART3]$

// $[USART4]
// [USART4]$

// $[USART5]
// [USART5]$

// $[USB]
// [USB]$

// $[VDAC0]
// [VDAC0]$

// $[WFXO]
// [WFXO]$

// $[WTIMER0]
// [WTIMER0]$

// $[WTIMER1]
// [WTIMER1]$

// $[WTIMER2]
// [WTIMER2]$

// $[WTIMER3]
// [WTIMER3]$

// $[CUSTOM_PIN_NAME]
#ifndef MOSI_SPI_DQ4_A16_PORT                   
#define MOSI_SPI_DQ4_A16_PORT                    gpioPortB
#endif
#ifndef MOSI_SPI_DQ4_A16_PIN                    
#define MOSI_SPI_DQ4_A16_PIN                     3
#endif

#ifndef MISO_SPI_DQ5_C17_PORT                   
#define MISO_SPI_DQ5_C17_PORT                    gpioPortB
#endif
#ifndef MISO_SPI_DQ5_C17_PIN                    
#define MISO_SPI_DQ5_C17_PIN                     4
#endif

#ifndef SPI_CLK_DQ6_A15_PORT                    
#define SPI_CLK_DQ6_A15_PORT                     gpioPortB
#endif
#ifndef SPI_CLK_DQ6_A15_PIN                     
#define SPI_CLK_DQ6_A15_PIN                      5
#endif

#ifndef SPI_CS_DQ7_C18_PORT                     
#define SPI_CS_DQ7_C18_PORT                      gpioPortB
#endif
#ifndef SPI_CS_DQ7_C18_PIN                      
#define SPI_CS_DQ7_C18_PIN                       6
#endif

// [CUSTOM_PIN_NAME]$

#endif // PIN_CONFIG_H

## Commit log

2023-09-06 Initial commit!
2023-09-06 Cleanup
2023-09-06 Folder structure
2023-09-07 Initialize KiCAD Project and set up Checkout System in README
2023-09-07 Gitignore KiCAD lock files
2023-09-07 Initialize KiCAD Project and set up Checkout System in README (#1)
2023-09-09 Update README.md
    Fix Typo
2023-09-11 Vivado in Non-Project mode
2023-09-11 Working Non-Project mode V1
2023-09-11 Fixed Syntax errors - script is functional
2023-09-12 readme edit
2023-09-12 add power supply files
2023-09-13 Final test for tcl-script: BITFILE GENERATED
2023-09-13 pcb: Add top-level layout, footprint and pinout for EFM32
    Added FPGA, EFM32GG footprint and pinout.
2023-09-13 Final cleanup (for now)
2023-09-13 SPI-interface for FPGA
2023-09-14 1. draft SPI-interface + tcl script for programming fpga
2023-09-14 More cleanup
2023-09-20 Working TCL-scripts + basic SPI-slave on FPGA
2023-09-20 mend
2023-09-20 Create hierarchical labels for base QSPI out from MCU
2023-09-20 Update PCB gitignore to ignore backups and auto_saved_files
2023-09-21 Trace MCU Master to SRAM Slave
2023-09-21 Finish MCU Master to Slave Traces for QSPI and Reorganize RootSheet
2023-09-21 Slight restructuring of FPGA SRAM Naming
2023-09-22 Start of a testbench for the SPI_Interface
2023-09-22 Trace QSPI for MCU Master (#7), slaves unconnected
2023-09-25 Add Local Library Component and Implement USB Mini Connector
2023-09-25 Attempt to set up SRAM
2023-09-26 pcb: cleanup mcu sram
2023-09-26 SPI Testbench "work-in-progress"
2023-09-26 pcb: cleanup fpga and put bank 34 in ddr
2023-09-26 fixup: pcb symbol
2023-09-26 ddr wip
2023-09-26 pcb: cleanup mcu sram (#10)
2023-09-27 dump
2023-09-27 1.5V added
2023-09-28 add barrel jack
2023-09-29 reworking the whole system
2023-09-29 Clean up MCU ++
2023-09-29 add usb micro and switches
2023-09-29 hdmi fix
2023-10-02 pcb: re-structured PCB schematic layout
2023-10-02 pcb: re-structured PCB schematic layout (#13)
2023-10-02 add power layout
2023-10-04 attempt at routing
2023-10-04 route VGA and QSPI
2023-10-04 add hdmi layout
2023-10-04 add missing tracks on hdmi
2023-10-04 Copy/Add power layout
2023-10-05 Add USB and JTAG debug for EFM
2023-10-05 Start of a TB environment
2023-10-06 FPGA core branch
2023-10-07 change usb footprint to usb3 footprint
2023-10-08 before
2023-10-08 after
2023-10-08 3d models
2023-10-09 more pcb routing
2023-10-09 redo power circuit and add heat sink
2023-10-11 pcb: Finalized routing without DDR3
    Added ground and power plane, layed out all the components, fanned out
    BGA. QSPI between FPGA->MCU->SRAM and MCU->SRAM is routed. Most is done
    but DRC does not pass so do not produce.
2023-10-11 pcb: re-structured PCB schematic layout (#17)
2023-10-11 fix power circuit and replace jtag debug
2023-10-11 mcu debug edit
2023-10-11 pcb: 3.3V voltage rails fixup and connected IC2
2023-10-11 fix heatsink
2023-10-11 Structs for easier data-handling + start of raytrace core
2023-10-11 route 2 separate QSPI buses to SRAM from FPGA
2023-10-11 struct for Ray
2023-10-11 Fix DRC errors + silkscreen and make logo
2023-10-11 Fix 3V3 power level to be more open and delete unused backups
2023-10-11 Fix 3V3 power level to be more open and delete unused backups (#19)
2023-10-11 pcb: fix unconnected items
2023-10-11 pcb: fix unconnected items (#20)
2023-10-12 edit jtag debug connector
2023-10-12 fix DRC errors and edit footprint vias
2023-10-12 pcb: Add buttons
2023-10-12 pcb: Add debug leds and pinout header for FPGA
2023-10-12 pcb: All hail hypnotoad
2023-10-12 pcb: Gurt X Hypno
2023-10-12 pcb: Gurt X Hypno (#26)
2023-10-12 pcb: mounting holes
2023-10-12 Start on datapath
2023-10-13 FSM for "outer" RayTrace core
2023-10-13 FSMs for RayTracing core and Tracing core
2023-10-15 First draft of raycore!
2023-10-15 Ignore waveform config file
2023-10-16 fpga: add vga and thread-sources from vivado
2023-10-17 Extra registers for value-control
2023-10-18 Updated register sizes
2023-10-23 Updated register sizes for calculations
2023-10-23 Module to find index of highest set bit
2023-10-23 Paper for calculating square roots on FPGAs
2023-10-23 Square root algorithm v1
2023-10-23 always_ff vs always_comb
2023-10-24 Waveform config
2023-10-24 Git ignored
2023-10-24 Testbench for square root solver
2023-10-25 Square root FSM
2023-10-25 Updated SquareRoot FSM
2023-10-26 Some bug away from a functioning square root solver
2023-10-26 fpga: Create basis for final rtl
2023-10-31 Working spi
2023-10-31 Added world things
2023-10-31 Updated square_root
2023-11-01 Modify spi to receive 64 bit
2023-11-05 Use sphere algorithm
2023-11-06 Updated gitignore
2023-11-07 Working square-root algorithm
2023-11-07 Migrate to 100T
2023-11-07 Implement sqrt into worker
2023-11-08 Implement fixed-point on discriminant-calculation and begin applying sqrt
2023-11-08 Refractor SquareRoot algorithm
2023-11-08 Fix up fixed-point calculation of discriminant
2023-11-09 Update spi to use accumulator
2023-11-11 Prettyfying of code
2023-11-11 Calculation of normal-vector in interception point of sphere and ray
2023-11-13 Cleanup in trailing whitespaces
2023-11-14 Fixed trailing whitespaces
2023-11-14 Implement normal into pipeline
2023-11-14 Division module
2023-11-14 Division module for accurate division
2023-11-14 WIP Division implementation
2023-11-14 WIP Division
2023-11-14 Multisphere start
2023-11-15 Beginning of multispheres
2023-11-15 Still no image of two spheres
2023-11-16 Simple led program
2023-11-16 Added extra states
2023-11-16 Small changes to be able to synthesize
2023-11-16 Ignoring wave-config files
2023-11-20 milestone
2023-11-20 Non-working attempt at two spheres
2023-11-21 Hotfix
2023-11-21 Working mayb
2023-11-21 blabla
2023-11-21 Final delivery
2023-11-22 mcu code on PCB
2023-11-22 folder
2023-11-22 Add references to generated files
2023-11-22 external mcu prog
2023-11-22 Add report
